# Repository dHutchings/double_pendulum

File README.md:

# double pendulum

A battery-powered low power double pendulum.  Useful for looking cool.  It's a good gift.

[Video of Final](https://youtu.be/Yj28coDq9EA)

[Video of Rev 3 Prototype](https://youtu.be/eYqc_CuFVBs)

[Video of Rev 2 Prototype](https://youtu.be/RyoI87ninAo)

[Video of Rev 1 Prototype](https://www.youtube.com/watch?v=9qNsIy8OKPE)

[Video of Proof of Concept](https://youtu.be/A4e-QBMb_Hc)

[Video of Back EMF Demo](https://youtu.be/CLvjtHWwjVc)

[BOM](https://docs.google.com/spreadsheets/d/1zQ9JefeK5bJ6EfoIBReY1vUxNtvPFnJwqca2jpHTiHs/edit#gid=1877369656)

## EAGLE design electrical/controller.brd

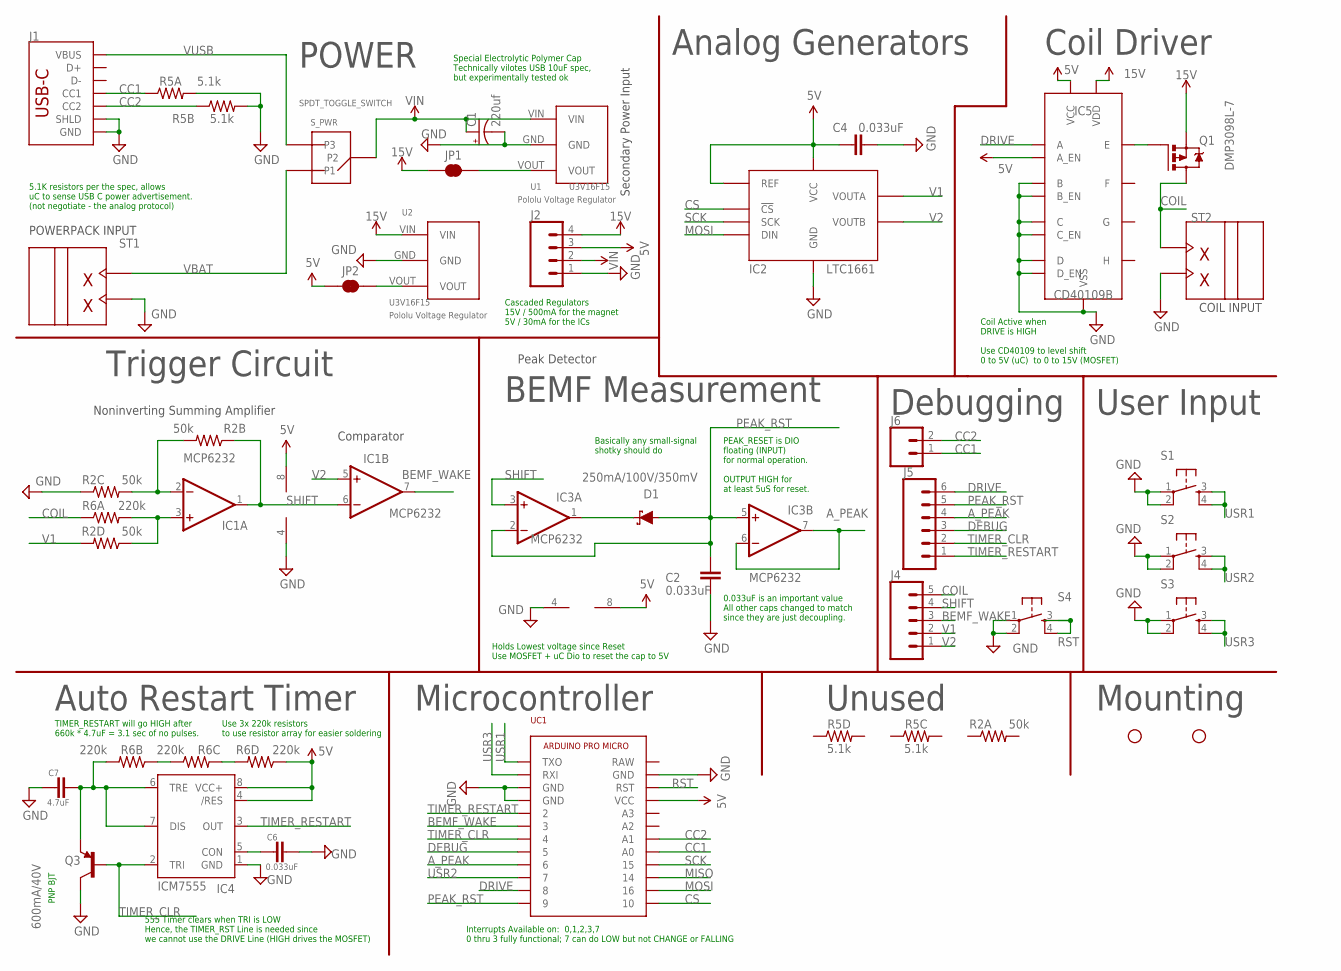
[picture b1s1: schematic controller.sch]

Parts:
C1: 220uf; E2,5-7
C2, C4, C6: 0.033uF; 0603-CAP
C7: 4.7uF; 0603-CAP
D1: 250mA/100V/350mV; SOD-323
IC1, IC3: MCP6232; SO08
IC2: LTC1661MSOP8; SOP65P490X110-8N
IC4: ICM7555; SO08
IC5: CD40109B; SOP65P640X120-16N
J1: USB_C_2-LAYER_PADS; USB-C-16P-2LAYER-PADS
J2: CONN_041X04_NO_SILK; 1X04_NO_SILK
J4: CONN_05NO_SILK; 1X05_NO_SILK
J5: CONN_06NO_SILK_NO_POP; 1X06_NO_SILK
J6: CONN_021X02_NO_SILK; 1X02_NO_SILK
JP1, JP2: JUMPER-SMT_2_NC_TRACE_SILK; SMT-JUMPER_2_NC_TRACE_SILK
Q1: DMP3098; SOT23-3
Q3: 600mA/40V; SOT23-3
R2: 50k; 1206_RA
R5: 5.1k; 1206_RA
R6: 220k; 1206_RA
S1, S2, S3, S4: TAC_SWITCHPTH; TACTILE-PTH
ST1, ST2: 2PIN_SCREW
STANDOFF1, STANDOFF2: STAND-OFFKEYSTONE_SMT_STANDOFF; KEYSTONE-4881
S_PWR: SPDT_TOGGLE_SWITCH; E-SWITCH-SPDT
U1: U3V16F15; POLOLU_VOLTAG_REGULATOR_U3V16FX_VERT
U2: U3V16F15; POLOLU_VOLTAG_REGULATOR_D45V1E1FX_VERT
UC1: ARDUINO_PRO_MICROUSBC; ARDUINO_PRO_MICRO_USBC

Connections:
5V: C4.1, IC1.8 (V+), IC2.4 (REF), IC2.6 (VCC), IC3.8 (V+), IC4.4 (/RES), IC4.8 (VCC+), IC5.1 (VCC), IC5.2 (A_EN), J2.3, JP2.1, R6.P4 (1), UC1.VCC
15V: IC5.16 (VDD), J2.4, JP1.1, Q1.2 (S), U2.VIN
A_PEAK: IC3.6 (-IN), IC3.7 (OUT), J5.4, UC1.6
BEMF_WAKE: IC1.7 (OUT), J4.3, UC1.3
CC1: J1.A5 (CC1), J6.1, R5.P1 (1), UC1.A0
CC2: J1.B5 (CC2), J6.2, R5.P2 (1), UC1.A1
COIL: J4.5, Q1.3 (D), R6.P1 (1), ST2.P$2
CS: IC2.1 (!CS), UC1.10
DEBUG: J5.3, UC1.5
DRIVE: IC5.3 (A), J5.6, UC1.8
GND: C1.-, C2.2, C4.2, C6.2, C7.1, IC1.4 (V-), IC2.7 (GND), IC3.4 (V-), IC4.1 (GND), IC5.6 (B), IC5.7 (B_EN), IC5.8 (VSS), IC5.9 (C_EN), IC5.10 (C), IC5.14 (D), IC5.15 (D_EN), J1.GND, J1.GND2 (GND), J1.SHLD1 (SHLD), J1.SHLD2 (SHLD), J1.SHLD3 (SHLD), J1.SHLD4 (SHLD), J2.1, Q3.3 (C), R2.P3 (1), R5.P7 (2), R5.P8 (2), S1.1, S1.2, S2.1, S2.2, S3.1, S3.2, S4.1, S4.2, ST1.P$1, ST2.P$1, U1.GND, U2.GND, UC1.GND@0 (GND), UC1.GND@1 (GND), UC1.GND@2 (GND)
MISO: UC1.14
MOSI: IC2.3 (DIN), UC1.16
unnamed: D1.C, IC3.1 (OUT)
unnamed: R6.P2 (1), R6.P3 (1)
unnamed: IC1.3 (+IN), R2.P4 (1), R6.P8 (2)
unnamed: IC1.2 (-IN), R2.P6 (2), R2.P7 (2)
unnamed: C6.1, IC4.5 (CON)
unnamed: C7.2, IC4.6 (TRE), IC4.7 (DIS), Q3.2 (E), R6.P7 (2)
unnamed: JP1.2, U1.VOUT
unnamed: JP2.2, U2.VOUT
unnamed: R6.P5 (2), R6.P6 (2)
unnamed: IC5.4 (E), Q1.1 (G)
PEAK_RST: C2.1, D1.A, IC3.2 (-IN), IC3.5 (+IN), J5.5, UC1.9
RST: S4.3, S4.4, UC1.RST
SCK: IC2.2 (SCK), UC1.15
SHIFT: IC1.1 (OUT), IC1.6 (-IN), IC3.3 (+IN), J4.4, R2.P2 (1)
TIMER_CLR: IC4.2 (TRI), J5.2, Q3.1 (B), UC1.4
TIMER_RESTART: IC4.3 (OUT), J5.1, UC1.2
USR1: S1.3, S1.4, UC1.TXO
USR2: S2.3, S2.4, UC1.7
USR3: S3.3, S3.4, UC1.RXI
V1: IC2.8 (VOUTA), J4.2, R2.P5 (2)
V2: IC1.5 (+IN), IC2.5 (VOUTB), J4.1
VBAT: ST1.P$2, S_PWR.P1
VIN: C1.+, J2.2, S_PWR.P2, U1.VIN
VUSB: J1.VBUS1 (VBUS), J1.VBUS2 (VBUS), S_PWR.P3

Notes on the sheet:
POWERPACK INPUT
Secondary Power Input
COIL INPUT
Trigger Circuit
POWER
Noninverting Summing Amplifier
Comparator
Analog Generators
Debugging
Coil Driver
User Input
Mounting
Interrupts Available on: 0,1,2,3,7 0 thru 3 fully functional; 7 can do LOW but not CHANGE or FALLING
5.1K resistors per the spec, allows uC to sense USB C power advertisement. (not negotiate - the analog protocol)
PNP BJT
DMP3098L-7
Coil Active when DRIVE is HIGH Use CD40109 to level shift 0 to 5V (uC) to 0 to 15V (MOSFET)
555 Timer clears when TRI is LOW Hence, the TIMER_RST Line is needed since we cannot use the DRIVE Line (HIGH drives the MOSFET)
Auto Restart Timer
Microcontroller
BEMF Measurement
Peak Detector
Holds Lowest voltage since Reset Use MOSFET + uC Dio to reset the cap to 5V
Cascaded Regulators 15V / 500mA for the magnet 5V / 30mA for the ICs
TIMER_RESTART will go HIGH after 660k * 4.7uF = 3.1 sec of no pulses.
PEAK_RESET is DIO floating (INPUT) for normal operation. OUTPUT HIGH for at least 5uS for reset.
0.033uF is an important value All other caps changed to match since they are just decoupling.
Basically any small-signal shotky should do
Use 3x 220k resistors to use resistor array for easier soldering
Unused
Special Electrolytic Polymer Cap Technically vilotes USB 10uF spec, but experimentally tested ok

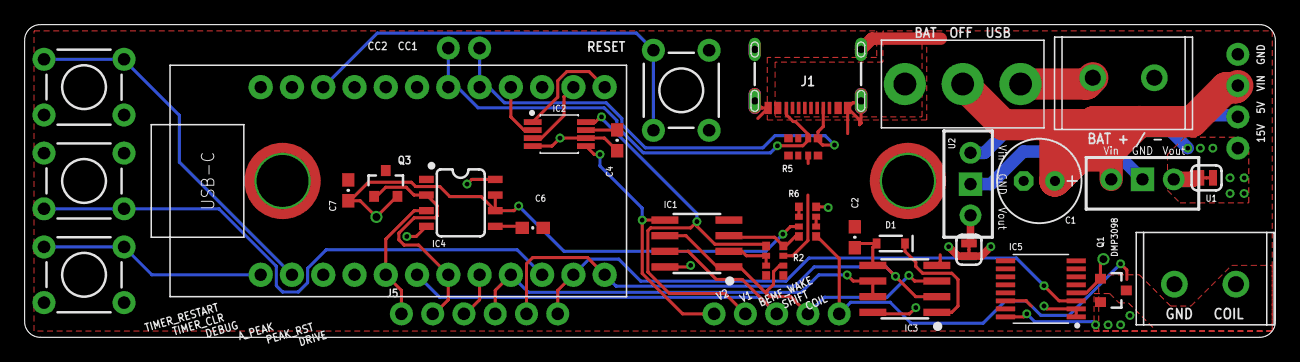
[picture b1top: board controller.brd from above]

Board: 2 copper layers, 101.6 x 25.4 mm, 35 parts (0 on the bottom side), 36 nets.

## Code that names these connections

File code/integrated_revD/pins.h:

#ifndef PINS_H
#define PINS_H

//PinDefs.

//the most important pins, related to sensing zero crossing + pushing
int bemf_wake = 3;  //pin 3, which can trigger an interrupt for waking up from power down.
int drive_mosfet = 8;  //pin 8... for turning the MOSFET on / pushing the magnet through the level shifter.

//pins for automatic missing pulse restarting.
int auto_timer_restart = 2; //pin 2... hooked up to the 555 timer - used for measuring when the 555 timer says its time to restart
int timer_clr = 4; //pin 4... hooked up to the 555 timer - used for clearing the timer.

//pins for measuring USB power capability
int cc1 = A0;
int cc2 = A1;

//pins for measuring the peak voltages
int a_peak = A7; //pin 6, but, for reasons surpassing understanding you do really need to say A7 //https://forum.arduino.cc/t/analogread-returns-varying-values-when-connected-to-gnd-3-3v-5v/460706
int a_peak_rst = 9;

//SPI capabilities
int cs = 10; 
//the rest of the pins are default: MISO on 14, MOSI on 16, SCK on 15.

//UI buttons
int faster = 1;  //Switch S3 (right)
int slower = 0;  //Switch S1 (left)
int start = 7;  //pin 0, Switch S2 (middle)












#endif

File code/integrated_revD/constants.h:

#ifndef CONSTANTS_H
#define CONSTANTS_H


/* Kinematics Constants: PUSH TIME  */
static long NOMINAL_PUSH = 7750; //nominal push time, fixed value that we always use.
static long MAX_PUSH = 25000;
static long MIN_PUSH = 500;
static long PUSH_SETTING_STEP = 250;

volatile long push_time_us = NOMINAL_PUSH;  //actual push time.  It needs to be here, since multiple code segments deal with it.  Can be adjusted up and down via button presses

/* pump more energy into the pendulum just after a restart */
long RESTART_EXTRA_PUSH_AMOUNT = 4000; //extra amount to push after I just restarted.
int RESTART_EXTA_PURHSES_COUNT = 30; //at a decreasing amount for these number of pushes.

/* and RANDOMNESS so we can break out of limit cycles */
volatile long RANDOM_AMOUNT = 2000; //allow for +/- 2000uS push time randomness... used to prevent long-term cyclic oscilations.  Same as the 40% of the push time it was in rev C
volatile long random_time; //random value, can have a negative value so not unsigned.  This is actually the dyamically computed random value

#define SCALE_RANDOMNESS true //set to true to enable the amount of randomness to be scaled up and down by how much we are over or underpushing, not just some nominal value.
//the real random push time will be scaled up or down from this value.  EG the nominal push time is 5500uS.  If it's half of that (2750 uS), the nominal random time max could cause a negative push time.

#define OUTSTRECHED_ARM_DETECTION true //set to true to enable BEMF sensing noticing that the pendulum is too fast to temporarily suspend pushes
#define OUTSTRECHED_ARM_SLOWING false //set to true to enable BEMF sensing noticing that the pendulum is too fast to slow down the push speed

volatile int MAX_PUSHES = 3; //number of times the pendulum will push untill is chooses a new random push time
volatile int CHANCE_NO_PUSH = 5; //10% chance of not pushing this time, b/c randomness.  Set to -1 to turn off.



#define USE_POST_PUSH_TIMEOUT true //set to true to enable a timeout after restarts or pushes - any BEMF triggers in this timeout are ignored.  Cuts down on spurious / power wasting double pushes
period_t SLEEP_TIMEOUT = SLEEP_120MS; //a randomly chosen good number

//Other Stuff

volatile float last_bemf; //the value of the most recent BEMF

volatile int NUM_PUSHES_BETWEEN_RESTARTS = 0;
volatile int NUM_RESTARTS_SINCE_UI_CHANGE = 0;
volatile int NUM_PUSHES_TO_SKIP = 0;

#define DEBUG false //set to true for debug-only TX / RX LEDs.  TX LED (left?) is generally around the drive interrupt trigger times, RX is around the MOSFET driving.

/* DEBUG Print Modes */
#define GENERAL_DEBUG_PRINTS false //set to tue for debug-only prints.  This means the system cannot power down (USB issues).  ALSO, be aware that if the serial monitor window isnt open but we are still trying to send prints, the pendulum will stop working, too.
#define SPEED_DEBUG_PRINTS false //prints to show the BEMF speed.
#define MOD_DEBUG_PRINTS false //wakeup-mode prints.  These things fill the screen
#define COUNT_PRINTS false //set to true to show count of the various pushes / restarts

#define DEBUG_PRINTS false //must be set to the OR of any of the above prints.  If at any one (at least) of the above is true, this must be true too.  ORs aren't working for whatever reason.

/* DEBUG Modes */
#define NO_PUSH false //set to true for absolutely no pushing or driving on the COIL wire.
#define RESET_EEPROM true
#define USE_RESTART true

/* Curve Threshold Sensing Offsets */
float voltage_add = 1.2;  //Shift the voltage curve measured from the coil of wire up by 2 volts.  We set the V1 to be 1.2V and the op-amp resistor feedback network will scale the COIL and shift it up by 2.
float voltage_threshold = 1.65;  //Set the threshold to generate an trigger for the interrupt in to 1.65 volts.  Therefore, the voltage cuve must be -.35V to change the comparator's output.  The interrumpt will be generated low-to-high just before the zero point.


#endif

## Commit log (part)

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2016-12-10 Second draft of code, add .gitignore.
2016-12-11 Interrupt based code
    No code in loop, whole code operates on interrupts. On track for power
    down modes.
2016-12-12 First draft of schematic.
    Routing begins now.
2016-12-12 Route Done
2016-12-12 Added global Attributes
2016-12-13 Created simple README
2016-12-19 Various low-power tests
2016-12-21 Sparkfun code to run DACs
2016-12-21 More fleshed-out DAC code
    Handles writing floats, different addresses, and EEPROM.
2016-12-21 WIP integration
    Things are currently very, very, broken in the electrical realm.
2016-12-22 Modified startup behavior
    Re-order code so that the interupts start triggering immediately after
    mosfet turns off last time of start sequence.
2016-12-22 Added extra DAC startup modes
    Allowing easy use of eeprom modes.
2016-12-22 Add two libraries for software i2c
2016-12-22 Minor renaming, restore power-down state.
2016-12-22 More code cleanup
2016-12-23 added more flexibility for thresholding.
    Turns out uC requires significant time (~2.3 ms) to wake from powerDown
    from an interupt.
    SO have to change the timing constants to account for this to get
    maximum push.
2016-12-30 small border change.
2016-12-31 Add Rev D mechanical
    Fixes issues describe in issue tracker + others.
2017-01-05 Add slight randomness in pushing time
    It makes the pendulum look more interesting. Also possibly more
    resistant to never-ending rapid cycles.
    also adjusted the push time down... the pendulum seems to have
    significant wear-in time.
2017-01-13 Changes to Rev D based on testing
    Re-worked several things about base & plate, such as material choice (brass to make heavier), more tapped holes, etc
    Added holes for zipties to pillar
    added material notes to every drawing & other changes to drawing frames
    added overall BOM w/ color images as another drawing
    Fixed battery holder dimmensions
2017-01-14 Autogenerated Docupacket
2017-01-15 Fixed images on color full assembly drawing
2017-01-17 New docu packet with laser stencil
2017-01-17 Fixed top link drawing
    It now is actually a drawing of the top link assembly.
2017-02-01 Fix Rev B erratta
    Hole sizes for screw terminals
    Pour clearance
    Silkscreen Fixes
    Revision Numbers
2017-03-03 New Plaque layout, and mechanical alignment jig
2017-03-13 Add restart button
    Middle button can now be used to restart pendulum, w/out changing
    contants. (Start vs Reset)
2017-12-14 Update README with links to final videos.
2017-12-14 Update distribution
    Doing to give #8 to Dr. Nelson, seeing as i'm still working in professor Agogino's lab.
2018-05-22 Update distribution b/c leaving Sapphire Motors
2018-05-25 Gave pendulums to more people
2025-03-26 drawings for new brass base
2025-06-17 Finally reasonable progress on the electronics
    This plus github.
    Nearly done fleshing the SCH out.
    Routing should not be difficult, just a few hours.
    Postponing changing the power parts of this circuit untill after the
    spools are done. Everything but the power, I can do now --> ship a
    revision, test it.
2025-06-18 Add gerber that exports slots for oshpark
2025-06-24 Create 3d model of PCB from Eagle
2025-06-30 Create skeleton code for rev D hardware based on rev C code.
2025-06-30 update integrated revD code to use new DAC and i2c lines.
2025-06-30 Correct comment on SCH
    Yes, the i2c address is reconfigurable, but hte default is 0x60
2025-07-08 Log Back EMF from legacy electromagnet via O-scope, replicate via DDS Signal Gen
2025-07-17 Ignore solidworks temporrary files
2025-07-17 add magnetic model in FEMM for old & new spool
    Still need to document it - at least take a picture of the
2025-07-17 some but not all of the changes for Rev D2
2025-07-18 Most, but not all, of rev D2
    Still need to test CC1 / CC2.
    Add debug pinout silkscreen labels.
    See if we can still use resistor arrays.
    Calculate new values for the trigger op-amp network.
2025-07-19 Calculate resistor values for new coil
2025-07-24 Add missing pullup; tweak slots for JLCPCB fab
2025-07-24 Final JLPCPCB fab files for rev D2
2025-08-01 Begin small changes to the plaque image
2025-08-06 Simple timing & mosfet test code
2025-08-08 better power test which includes start-up times.
2025-08-08 First pass of new code for rev D2
    just the basic functionality + new pins
2025-08-08 Make button presses smaller incriments
    This is because D2 is pushing a heck of a lot more agro than C, mostly
    b/c of the whole "booting up faster" thing.
2025-08-08 POC - Use configurable Timer to wake up at configurable duration
    MVP Demo of using Timer1 to wake up from Idle at a user-configurable
    time with high accuracy for times less than 8.3 seconds.
    So far, it only lets us use idle, so we can get 17uA - which, to be
    fair, is better than 30.
    I should put this solution on the github!
2025-08-08 Some tweaks for power saving and better pushing.
2025-08-08 More correct power down
2025-08-09 Come up with clever way to reduce part count (minus one mosfet & one resistor)
    See "electrical changes" todo when I get back D2.
    This code works when the circuit is modified as described on github.
2025-08-09 Add more power, duration tests.
    Turns out that the Low Power library's durations aren't precise -
    they're approximate.
    The only way to do precise powerdowns seems to be by leveraging Timer1 /
    Timer3 calling some interrupt as a way to get us out of the Idle mode.
    Works only for IDLE.
    Thus -->
2025-08-09 Move push out of ISR into loop; add more power reducing modes
    Keeping all the ISRs short (again, cardinal rule) and moving PUSH and
    RESTART into loop allows us to use the precise idle we developed a few
    commits ago.
2025-08-09 Cleanup + more Debug LEDs
2025-08-10 Various obscure power saving tests according to the datasheet
2025-08-14 Helpful tool for modifying the standoffs for the linkages
2025-08-14 Slight update to switch footprint
2025-08-15 Plop some things onto the PCB, lots of work to do.
2025-08-16 Clean up SCH
2025-08-16 Tweak positions, final D3 for prod
2025-10-18 commit a missing step
2025-10-24 Make prints more stable
    And informative, we get a print each time there's a new push time
    calculated.
    I do think we have an issue with negative push times...
2025-10-24 New Mode: Scaled randomness
    Really helps at low push values, even if now we don't have the bug of
    nearly infinite waiting. Makes the pendulum noticably less energetic at
    low push values, exactly what we want.
2025-10-24 Make 555 test closer to current rev Hardware
2025-10-24 Fix 555 functionality; Cleanup wakup interrupt naming convention
    555 wake up function errantly also touched the pins for the 555 timer,
    putting the 555 timer into a wrong state.
    555 auto restarting is now tested to work; again.
2025-10-26 Save UI-commanded push time in EEPROM
    Finally. That way, if the user decides that things need to be slower,
    they can be even after a power cycle.
2025-11-15 Tweak naming and prints to make the power_test more identical to code
2025-11-16 New debug mode
2025-11-16 Fix pinout
2025-11-16 New debug mode.
2025-11-19 Fix debug modes (minorly)
2025-11-20 Fix when DEBUG is false, for reasons I don't understand
    start_pendulum was hanging when #DEBUG was false.
    The hanging was coming from precise_idle. I have no idea why.
    Switching to more normal delays fixes it. Again, no idea why.
2025-12-04 Fix pins for new rev
2025-12-04 Rework restart & Randomness so the pendulum starts more reliably
    Two innovations:
    1) pump extra energy into the pendulum near the time of the restart
    2) don't do the open-loop pushes as much, head straight to the better
    pushes.
    Also, increase the nominal push time... it honestly seems to help make
    the rev D3 pendulum more like rev C. I'm seeing high-energy limit cycle
2025-12-04 Rename some functions
    Not all, but some.
2025-12-06 Fix BEMF sensing to measure at a better time
    No o-scope, but on rev D with the op-amp that can keep up, it makes
    sense if we measure BEMF after the push we might have measured some
    flyback somwhere.
    Via prints, its tested to help massively in measuring more sensical
    speeds.
2025-12-06 Add BEMF sensing statistics for the outstreched arm condition
2025-12-06 Fix oversight: Errant restarting while skipping pushing
2025-12-12 battery test data
    The new system seems to be worse b/c it keeps on getting stuck. When it
    gets un-stuck, it needs serious power via the auto-restart function.
    This feels more mechanical than electrical.
2025-12-13 New test
2025-12-14 Drive MOSFET at more optimum time, per issue tracker #22
    Will do better than this, but driving the MOSFET closer towards the peak
    BEMF really helps.
2025-12-15 put BEMF into volts
2025-12-15 Tweak randomness behaviour: don't randomly not push during startup
2025-12-15 Fix tests: Filename / 24:00:00 is invalid time (manually edit)
2025-12-16 play with x-axis time formats to make it easier to figure out the test
    If I zoom far enough out, it will show me elapsed Hours.
    If I zoom in, it starts showing me minutes / seconds.
2025-12-19 MOre tests
    next step is the whisker-style plot to make it much easier to deduce if
    the reset happened in htat interval
2025-12-28 Fix many erratta, overhaul power planes
    Rev D4 now WIP.
2025-12-31 Production Gerbers
2026-01-02 Much analysis
    Can now detect reset pulses.
    Have some metrics to show how many times reset fires. Could use a few
    more.
    I think that the battery life right now is mostly constrained by how
    often the pendulum resets, which is a combo of;
    1) How many reset attempts it takes to successfully reset.
2026-04-05 Some pin renaming to make things easier to understand...
2026-04-05 Put procesor to sleep & ingore all triggers after a push
    For about 120 ms.
    This cuts down the number of double-pushes that are errant and thus
    saves power.
    One full-up test went from 0.0255 to 0.0223 mean / average current
    draw.
    Hard to know for sure, but...
2026-04-07 New data: removing doublepushed significantly helped, but more required
    Still well below 100 hour performance of the rev C's.
    What's next:
    - Capacitor
    - Figure out some kind of better restart sequence (should I
    reverse-energize the magnet to pull in??)
2026-04-21 Ask chat GPT for a forced + damped double pendulum numeric simulator
2026-04-21 add complexity to the simulator.
    done by hand this time!
2026-04-22 New battery test
    Maybe not the most helpful one.
2026-04-25 (Mostly) fix debug prints
    some of hte power down modes break prints, some don't
    have to be careful with what I am using and when.
2026-04-26 Better visualizations: include geometry & links, energy plots
2026-04-27 Modify solver: respect 2pi and over-the-top wraparounds
    Unexpectedly a lot of work to do that.
    basically:
    1) Do not use directional zero-crossing. Instead, when pushing,
    completely ignore zero-crossing (which is how hte pendulum does it,
    anyway).
    2) if we don't deal with 2pi waparounds, we only push if we don't go
2026-04-27 New test permutation - see Issue #25
    Big improvement by adding a cap!
    Probably likely on rev C that the big cap was doing a lot of heavy
    lifting...
2026-05-02 Plot & Code cleanup
2026-05-03 Acutally use the reset button
2026-05-03 Bunch of modeling for amount of energy stored in magnetic attraction
    Turns out to not matter much, or all, really.
2026-05-03 Moar bugfixes
2026-05-05 Make restart better
    Rev D hardware doesn't need multiple pushes; just the first will do.
    Also remember to turn off the MOS when done.
2026-05-05 constant tweaking.
2026-05-24 Some tests, but not sure what the test conditions were associated with them
2026-06-01 Schematic Changes
2026-06-07 Thoughts about who will get new ones

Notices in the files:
parts and their libraries:
SparkFun-IC-Special-Function: Licensing: Creative Commons ShareAlike 4.0 International - https://creativecommons.org/licenses/by-sa/4.0
